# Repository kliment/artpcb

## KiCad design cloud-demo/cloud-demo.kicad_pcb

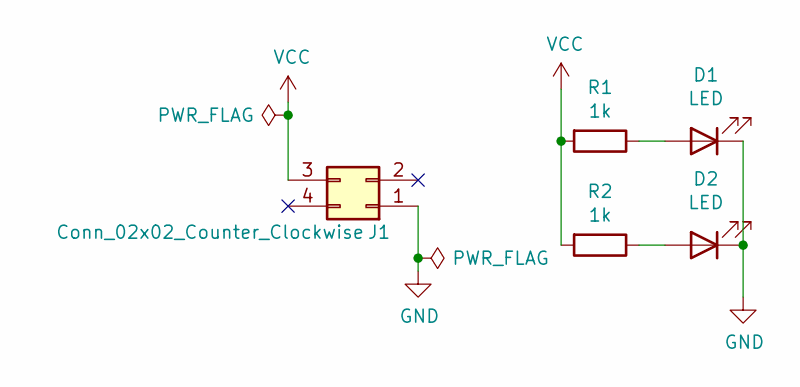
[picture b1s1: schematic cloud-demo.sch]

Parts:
D1, D2: LED; LED_0805_2012Metric_Pad1.15x1.40mm_HandSolder
J1: Conn_02x02_Counter_Clockwise; PinHeader_2x02_P2.54mm_Vertical
R1, R2: 1k; R_0805_2012Metric_Pad1.15x1.40mm_HandSolder

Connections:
GND: D1.1 (K), D2.1 (K), J1.1
unnamed: D1.2 (A), R1.1
unnamed: D2.2 (A), R2.1
VCC: J1.3, R1.2, R2.2

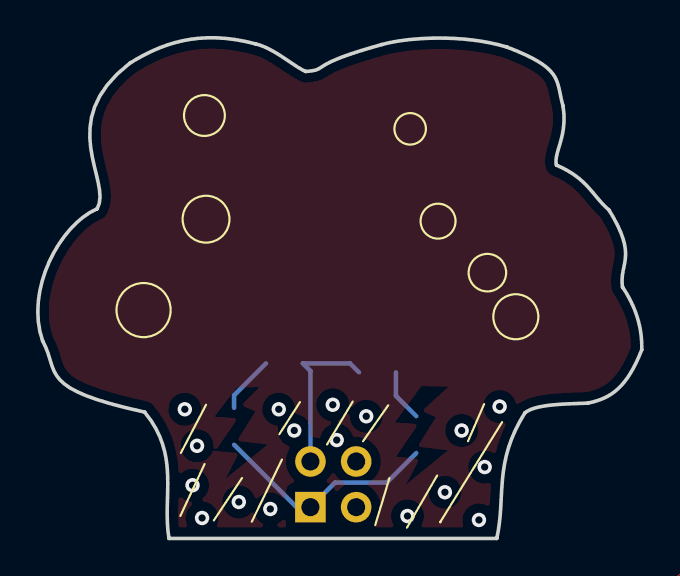
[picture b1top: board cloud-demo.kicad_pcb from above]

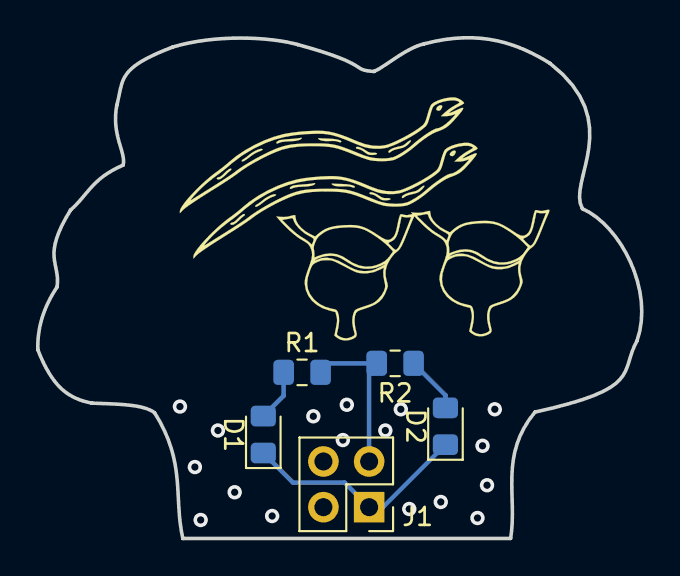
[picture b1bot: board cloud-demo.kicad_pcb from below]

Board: 2 copper layers, 33.6 x 27.8 mm, 5 parts (5 on the bottom side), 4 nets.

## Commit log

2020-07-31 Update demo projects
2020-07-31 add presentation
